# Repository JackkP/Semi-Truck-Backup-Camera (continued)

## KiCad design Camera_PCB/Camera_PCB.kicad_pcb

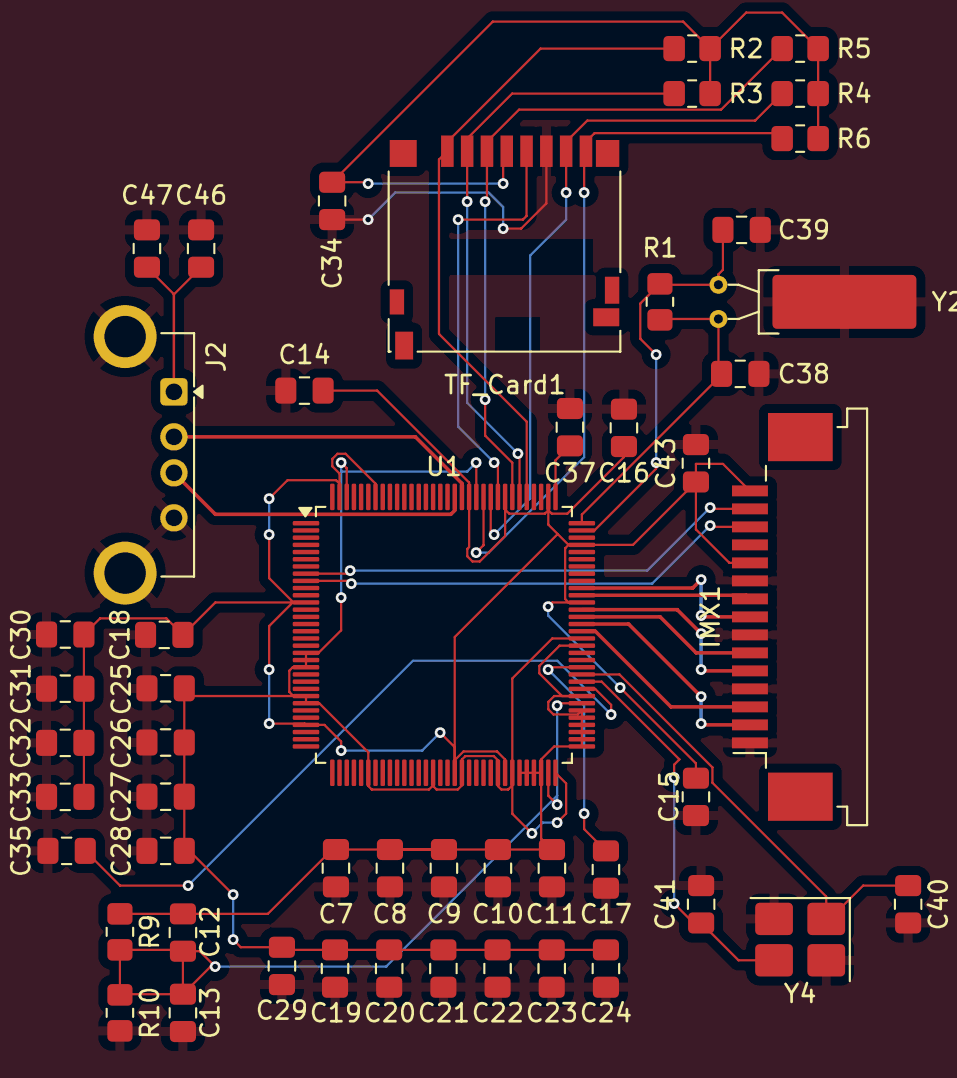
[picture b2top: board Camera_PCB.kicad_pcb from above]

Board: 6 copper layers, 51 parts (0 on the bottom side), 30 nets.

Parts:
C7, C19, C25, C30: 10uF; C_0805_2012Metric_Pad1.18x1.45mm_HandSolder
C8, C9, C20, C21, C26, C27, C31, C43, C47: 1uF; C_0805_2012Metric_Pad1.18x1.45mm_HandSolder
C10, C11, C12, C13, C14, C15, C16, C17, C18, C22, C23, C24, C28, C29, C32, C33, C34, C46: 104; C_0805_2012Metric_Pad1.18x1.45mm_HandSolder
C35: 240; C_0805_2012Metric_Pad1.18x1.45mm_HandSolder
C37: 4.7uF; C_0805_2012Metric_Pad1.18x1.45mm_HandSolder
C38, C39, C40, C41: 18pF; C_0805_2012Metric_Pad1.18x1.45mm_HandSolder
IMX1: TE_1-84952-5_1x15-1MP_P1.0mm_Horizontal
J2: USB_A; USB_A_Connfly_DS1095
R1: 10M; R_0805_2012Metric_Pad1.20x1.40mm_HandSolder
R2, R3, R4, R5, R6: 47k; R_0805_2012Metric_Pad1.20x1.40mm_HandSolder
R9, R10: 2k; R_0805_2012Metric_Pad1.20x1.40mm_HandSolder
TF_Card1: microSD_HC_Hirose_DM3D-SF
U1: V3s-eLQFP128; LQFP-128_14x14mm_P0.4mm
Y2: Crystal_GND3; Crystal_C38-LF_D3.0mm_L8.0mm_Horizontal_1EP_style1
Y4: Crystal_GND24; Crystal_SMD_3225-4Pin_3.2x2.5mm_HandSoldering

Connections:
+5V: C46.2, C47.2, J2.1 (VBUS)
CSI-SCK: IMX1.13 (CAM_SCL), U1.9 (PE21)
CSI_SDA: IMX1.14 (CAM_SDA), U1.8 (PE22)
GNDREF: C7.1, C8.1, C9.1, C10.1, C11.1, C13.1, C14.1, C15.1, C16.1, C17.1, C18.1, C19.1, C20.1, C21.1, C22.1, C23.1, C24.1, C25.1, C26.1, C27.1, C28.1, C29.1, C30.1, C31.1, C32.1, C33.1, C34.2, C35.1, C37.1, C38.2, C39.2, C40.2, C41.1, C43.2, C46.1, C47.1, IMX1.1 (GND), IMX1.4 (GND), IMX1.7 (GND), IMX1.10 (GND), J2.4 (GND), J2.5 (Shield), R10.2, TF_Card1.6 (GND), Y2.3, Y4.2, Y4.4
HPVCC: C14.2, C15.2, C16.2, C18.2, C30.2, C31.2, C32.2, C33.2, C43.1, IMX1.11 (CAM_EN0), IMX1.15 (CAM_3.3V), U1.12 (VCC-PE0), U1.29 (VCC-PE1), U1.50 (VCC-IO3), U1.57 (VCC-IO2), U1.85 (VCC-MCSI), U1.93 (EPHY-VCC), U1.98 (VCC-RTC), U1.104 (VCC-IO0), U1.109 (VCC-USB), U1.122 (HPVCCIN), U1.127 (VCC-IO1)
MCSI_CK_N: IMX1.8 (CSI_CLKN), U1.87 (MCSI-CKN)
MCSI_CK_P: IMX1.9 (CSI_CLKP), U1.86 (MCSI-CKP)
MCSI_D0_N: IMX1.2 (CSI_D0N), U1.82 (MCSI-D0N)
MCSI_D0_P: IMX1.3 (CSI_D0P), U1.81 (MCSI-D0P)
MCSI_D1_N: IMX1.5 (CSI_D1N), U1.84 (MCSI-D1N)
MCSI_D1_P: IMX1.6 (CSI_D1P), U1.83 (MCSI-D1P)
RTC-VIO: C37.2, U1.97 (RTC-VIO)
SDC0_CLK: TF_Card1.5 (CLK), U1.105 (PF2)
SDC0_CMD: R5.2, TF_Card1.3 (CMD/MOSI), U1.103 (PF3)
SDC0_D0: R4.2, TF_Card1.7 (DAT0/MISO), U1.106 (PF1)
SDC0_D1: R6.2, TF_Card1.8 (DAT1), U1.107 (PF0)
SDC0_D2: R2.2, TF_Card1.1 (DAT2), U1.101 (PF5)
SDC0_D3: R3.2, TF_Card1.2 (DAT3/CS), U1.102 (PF4)
SVREF: C12.1, C13.2, R9.2, R10.1, U1.63 (SVREF1), U1.71 (SVREF0)
SZQ: C35.2, U1.73 (SZQ)
USB_N: J2.2 (D-), U1.110 (USB-DM)
USB_P: J2.3 (D+), U1.111 (USB-DP)
VCC-DRAM: C7.2, C8.2, C9.2, C10.2, C11.2, C12.2, R9.1, U1.59 (VCC-DRAM8), U1.60 (VCC-DRAM9), U1.61 (VCC-DRAM10), U1.62 (VCC-DRAM11), U1.65 (VCC-DRAM0), U1.66 (VCC-DRAM1), U1.67 (VCC-DRAM2), U1.68 (VCC_DRAM3), U1.69 (VCC-DRAM4), U1.70 (VCC-DRAM5), U1.72 (VCC-DRAM6), U1.79 (VCC-DRAM7)
VCC-PLL: C17.2, U1.76 (VCC-PLL)
VDD: C34.1, R2.1, R3.1, R4.1, R5.1, R6.1, TF_Card1.4 (VDD)
VDD-CPU: C19.2, C20.2, C21.2, C22.2, C23.2, C24.2, C25.2, C26.2, C27.2, C28.2, C29.2, U1.19 (VDD-SYS3), U1.20 (VDD-CPU3), U1.21 (VDD-CPU2), U1.25 (VDD-CPU1), U1.26 (VDD-CPU0), U1.38 (VDD-CPU4), U1.47 (VDD-CPU5), U1.51 (VDD-CPU6), U1.56 (VDD-CPU7), U1.58 (VDD-SYS4), U1.64 (VDD-SYS5), U1.80 (VDD-SYS0), U1.108 (VDD-SYS1), U1.126 (VDD-SYS2)
X24MIN: C40.1, U1.75 (X24MIN), Y4.1
X24MOUT: C41.2, U1.74 (X24MOUT), Y4.3
X32KIN: C38.1, R1.1, U1.96 (X32KIN), Y2.1
X32KOUT: C39.1, R1.2, U1.95 (X32KOUT), Y2.2

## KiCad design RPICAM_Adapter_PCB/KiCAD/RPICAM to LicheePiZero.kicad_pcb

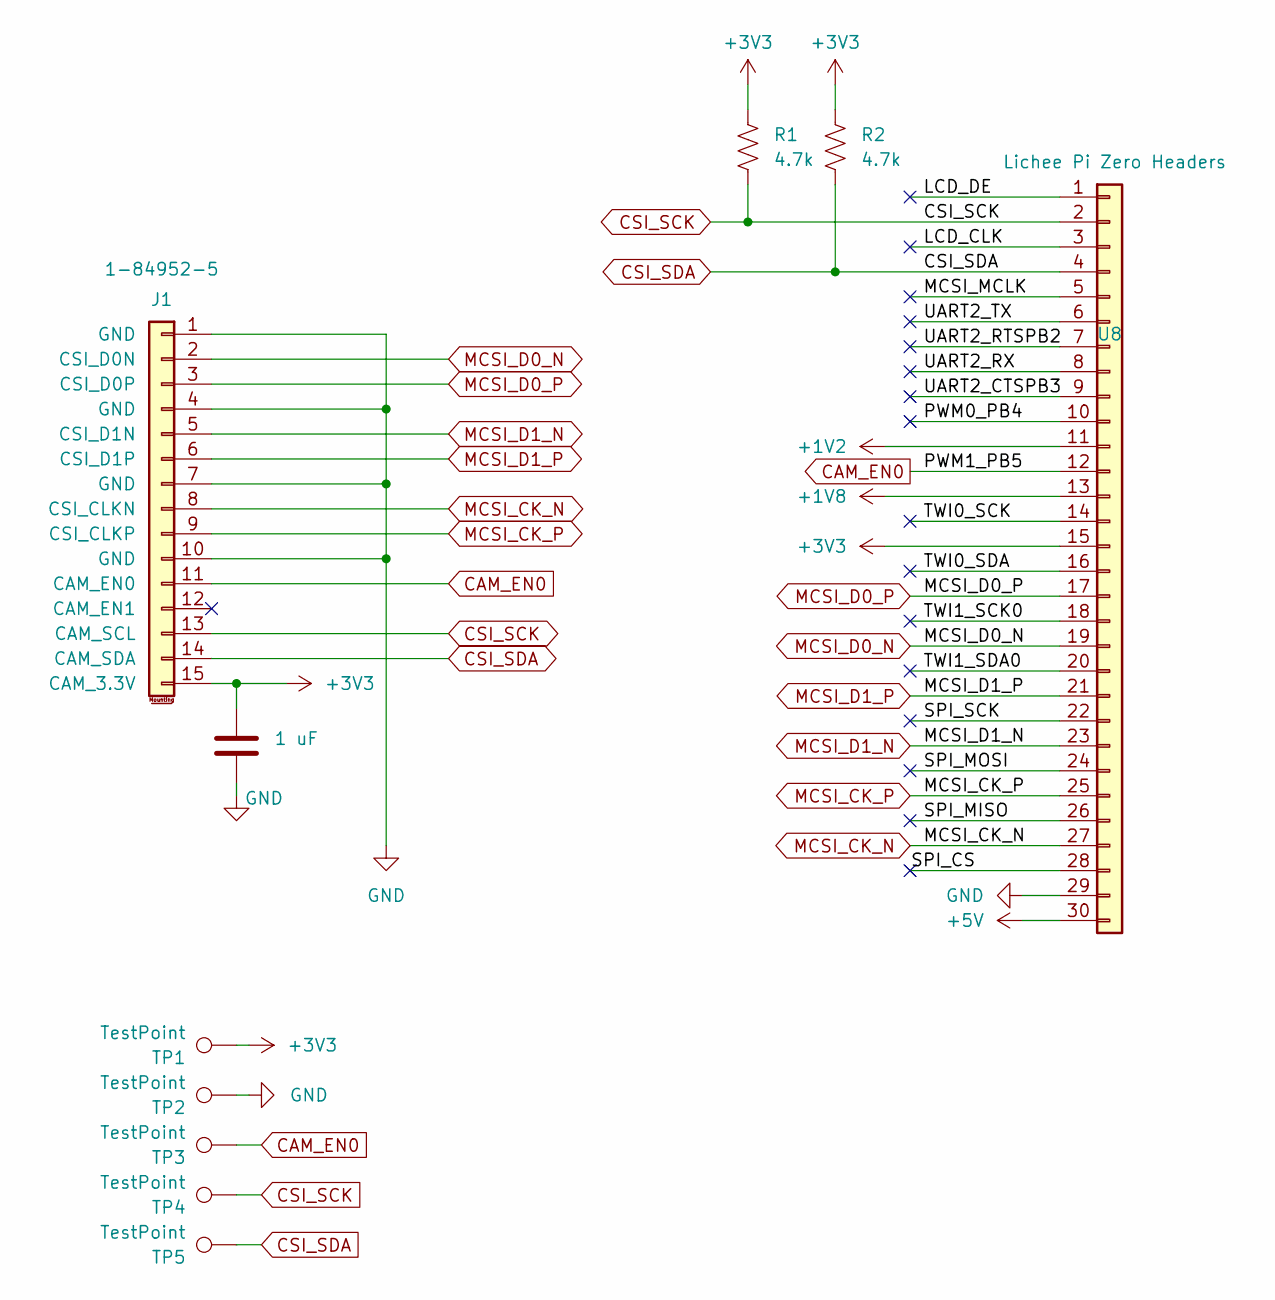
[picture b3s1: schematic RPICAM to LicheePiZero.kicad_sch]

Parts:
C1: 1 uF; C_0805_2012Metric_Pad1.18x1.45mm_HandSolder
J1: 1-84952-5; TE_1-84952-5_1x15-1MP_P1.0mm_Horizontal
R1, R2: 4.7k; R_0805_2012Metric_Pad1.20x1.40mm_HandSolder
TP1, TP2, TP3, TP4, TP5: TestPoint; TestPoint_Pad_D1.0mm
U8: Lichee Pi Zero Headers; PinHeader_1x30_P1.27mm_Vertical

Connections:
+1V2: U8.11
+1V8: U8.13
+3V3: C1.1, J1.15 (CAM_3.3V), R1.1, R2.1, TP1.1, U8.15
+5V: U8.30
/LCD_CLK: U8.3
/LCD_DE: U8.1
/MCSI_MCLK: U8.5
/PWM0_PB4: U8.10
/SPI_CS: U8.28
/SPI_MISO: U8.26
/SPI_MOSI: U8.24
/SPI_SCK: U8.22
/TWI0_SCK: U8.14
/TWI0_SDA: U8.16
/TWI1_SCK0: U8.18
/TWI1_SDA0: U8.20
/UART2_CTSPB3: U8.9
/UART2_RTSPB2: U8.7
/UART2_RX: U8.8
/UART2_TX: U8.6
CAM_EN0: J1.11 (CAM_EN0), TP3.1, U8.12
CSI_SCK: J1.13 (CAM_SCL), R1.2, TP4.1, U8.2
CSI_SDA: J1.14 (CAM_SDA), R2.2, TP5.1, U8.4
GND: C1.2, J1.1 (GND), J1.4 (GND), J1.7 (GND), J1.10 (GND), TP2.1, U8.29
MCSI_CK_N: J1.8 (CSI_CLKN), U8.27
MCSI_CK_P: J1.9 (CSI_CLKP), U8.25
MCSI_D0_N: J1.2 (CSI_D0N), U8.19
MCSI_D0_P: J1.3 (CSI_D0P), U8.17
MCSI_D1_N: J1.5 (CSI_D1N), U8.23
MCSI_D1_P: J1.6 (CSI_D1P), U8.21

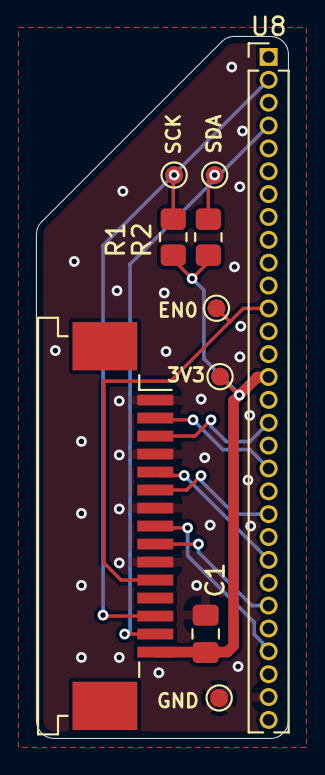
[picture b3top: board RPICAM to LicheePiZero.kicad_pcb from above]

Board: 2 copper layers, 14.0 x 39.0 mm, 10 parts (0 on the bottom side), 11 nets.

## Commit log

2025-09-22 Created Camera PCB Project
2025-09-24 Connors Branch
2025-09-24 Init V3S chip added
2025-09-26 Modified symbol to inclued alternate pin descriptions
2025-09-26 Added Most Power Inputs
2025-09-26 Fixed Capacitor Naming
2025-09-28 KiCAD Files for RPICAM to LicheePiZero Adapter PCB
2025-09-28 Some References for the Schematic
2025-09-30 Changed I2C interface for MIPI_CSI adapter board to use CSI TWI
2025-09-30 Formatting/referencing the "how to set up WAP.md
2025-10-01 Schematic updates
2025-10-03 This is the ordered version of the MIPI-CSI2 adapter PCB
2025-10-03 Camera connections added
2025-10-03 Pulled Adapter PCB files
2025-10-03 Readded Camera, USB connections
2025-10-04 Added x pins + text
2025-10-08 Changed usb -> A 2.0
2025-10-08 Switched pins 86, 87
2025-10-08 Create BatteryPower.kicad_sch-bak
2025-10-08 Initial Power Schem
2025-10-13 Started PCB
2025-10-15 restructuring main branch to have power schematic in power directory
2025-10-15 moved root readme back to root dir
2025-10-15 added prelimiinary linux build instructions
2025-10-18 more linux build crap
2025-10-18 USB working holy crap
2025-10-20 Update How to set up WAP.md (edited dnsmasq.conf)
    missing dhcp-authoritative in dnsmasq.conf for WAP setup
2025-10-21 created wpa_supplicant.conf and wpa_supplicant init.d script
2025-10-21 fixed wifi init script conflict
2025-10-21 adjustments to get wireless link setup complete and wireless streaming, had some problems getting video to stream since previous streaming commands were unencoding then re-encoding video stream. Vide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
2025-10-24 Commit Message
2025-10-29 trying to clean up PCB branch
2025-10-29 cleaned up PCB branch
2025-10-29 more PCB branch cleanup
2025-10-29 Updated Component Values for Power
2025-10-29 10/29 Footprint Additions
2025-10-31 Camera PCB Schematic review 1
2025-11-03 Schematic done, thoroughly reviewed by Jack, should get reviewed by Connor if possible.
2025-11-03 cleaned up Camera_PCB \repository
2025-11-04 Thorough Camera PCB Review by Jack
2025-11-04 more schematic changes, added solder bridges, etc
2025-11-05 PCB commit before reorganizing
2025-11-05 Shrunk camera PCB and rearranged connectors. Everything on board. Not everything connected.
2025-11-05 Only unconnected grounds in schematic. Still need to thoroughly clean up.
2025-11-06 replaced all power traces with zones
2025-11-07 PCB has no missing connections, (some missing grounds)
2025-11-07 Pre sd-card move
2025-11-09 Added 3d models, completed layout. Should still review more.
2025-11-10 ordered PCB V1.0
2025-11-10 generated gerbers for order
2025-11-11 resized vias to 0.2/0.45mm
2025-11-12 actual production gerbers after via resizing
2025-11-12 updated bom for order
2025-11-12 TCP Packet Transfer Code
